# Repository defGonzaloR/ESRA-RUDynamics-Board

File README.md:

# ESRA-RUDynamics-Board

This is V3 of the Rutgers Dynamics power distribution board, building off of the original board designed by the Columbia University Robotics team. This is also my first power distribution board design. 

I used a board-mounted XT90 connector to attach to the Lipo batteries. For circuit protection, I included fuse holders that connect to each output for the legs, as well as essential filtering for high-noise signals. At the bottom is a buck converter, to step down the 24V to 12V for powering the Jetson Orin Nano.

Due to funding, this board was discontinued, but I'm excited to apply skills and theory learned from this design to future applications.

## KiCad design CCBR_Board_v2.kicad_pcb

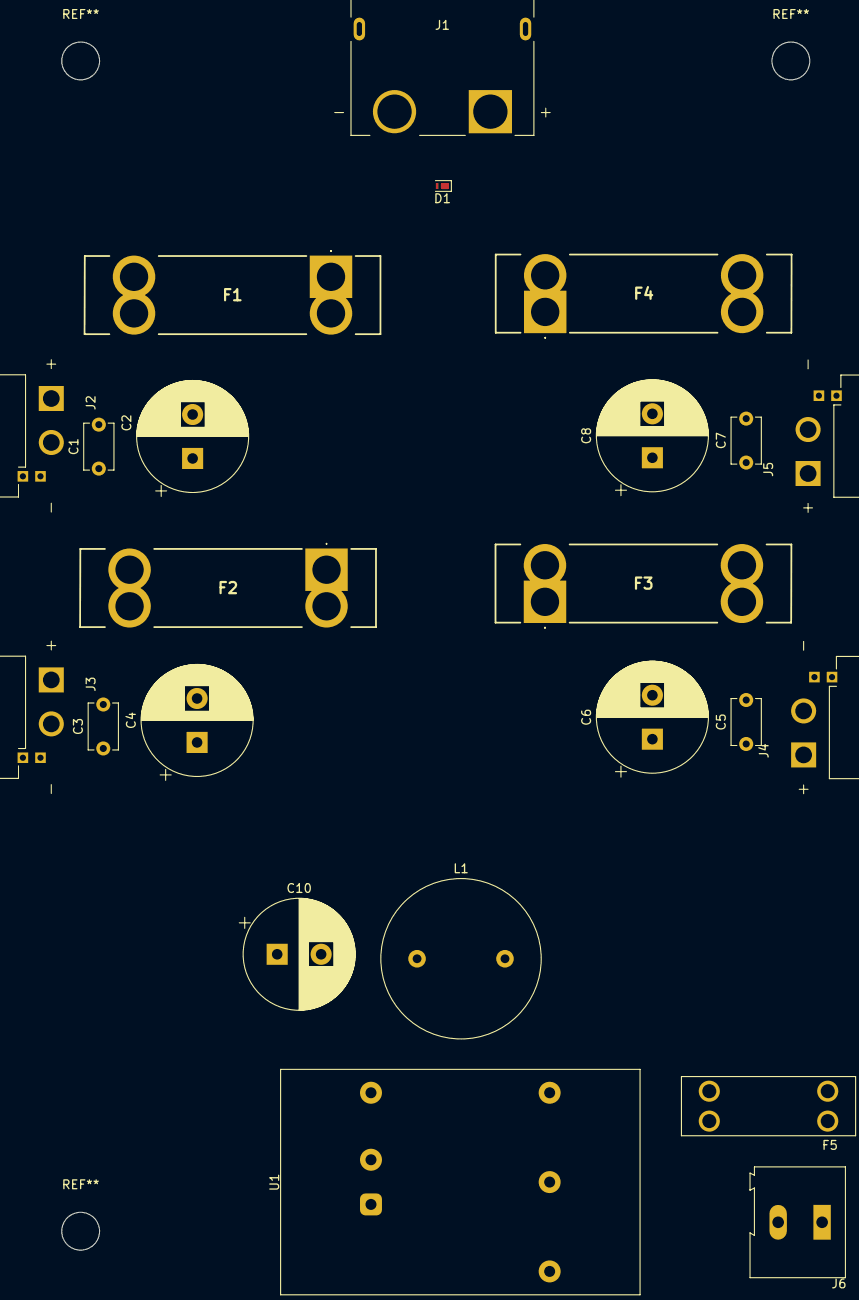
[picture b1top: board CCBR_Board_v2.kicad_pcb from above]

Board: 2 copper layers, 23 parts (0 on the bottom side), 7 nets, no tracks yet.

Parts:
C1, C3, C5, C7: 0.1 uF; C_Disc_D5.1mm_W3.2mm_P5.00mm
C2, C4, C6, C8: 470 uF; CP_Radial_D12.5mm_P5.00mm
C10: 100uF; CP_Radial_D12.5mm_P5.00mm
D1: PTVS26VZ1USK; Nexperia_DSN1608-2_1.6x0.8mm
F1, F2, F3, F4: Fuse; 3581
F5: Fuse; FUSE_3557-2
J1: Conn_01x02_Pin; AMASS_XT90PW-M
J2, J3, J4, J5: Conn_01x02_Socket; AMASS_XT30PW_2_2_-M.G.B
J6: Screw_Terminal_01x02; TerminalBlock_Altech_AK300-2_P5.00mm
L1: 0.47 uH; L_Radial_D18.0mm_P10.00mm
U1: JTD1548S12; Converter_DCDC_XP_POWER_JTDxxxxxxx_THT

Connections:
+24V: C10.1, D1.1 (K), F1.2, F2.2, F3.2, F4.1, L1.1
GND: C1.2, C2.2, C3.2, C4.2, C5.2, C6.2, C7.2, C8.2, C10.2, D1.2 (A), J6.2, U1.2 (-VIN), U1.5 (-VOUT)
unnamed: C1.1, C2.1, F1.1
unnamed: C3.1, C4.1, F2.1
unnamed: C5.1, C6.1, F3.1
unnamed: C7.1, C8.1, F4.2
unnamed: L1.2, U1.1 (+VIN)

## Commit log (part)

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2026-05-03 Add files via upload
    Current iteration of board redesign
